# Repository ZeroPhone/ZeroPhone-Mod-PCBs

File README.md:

# ZeroPhone-Mod-PCBs
ZeroPhone mod board PCB files

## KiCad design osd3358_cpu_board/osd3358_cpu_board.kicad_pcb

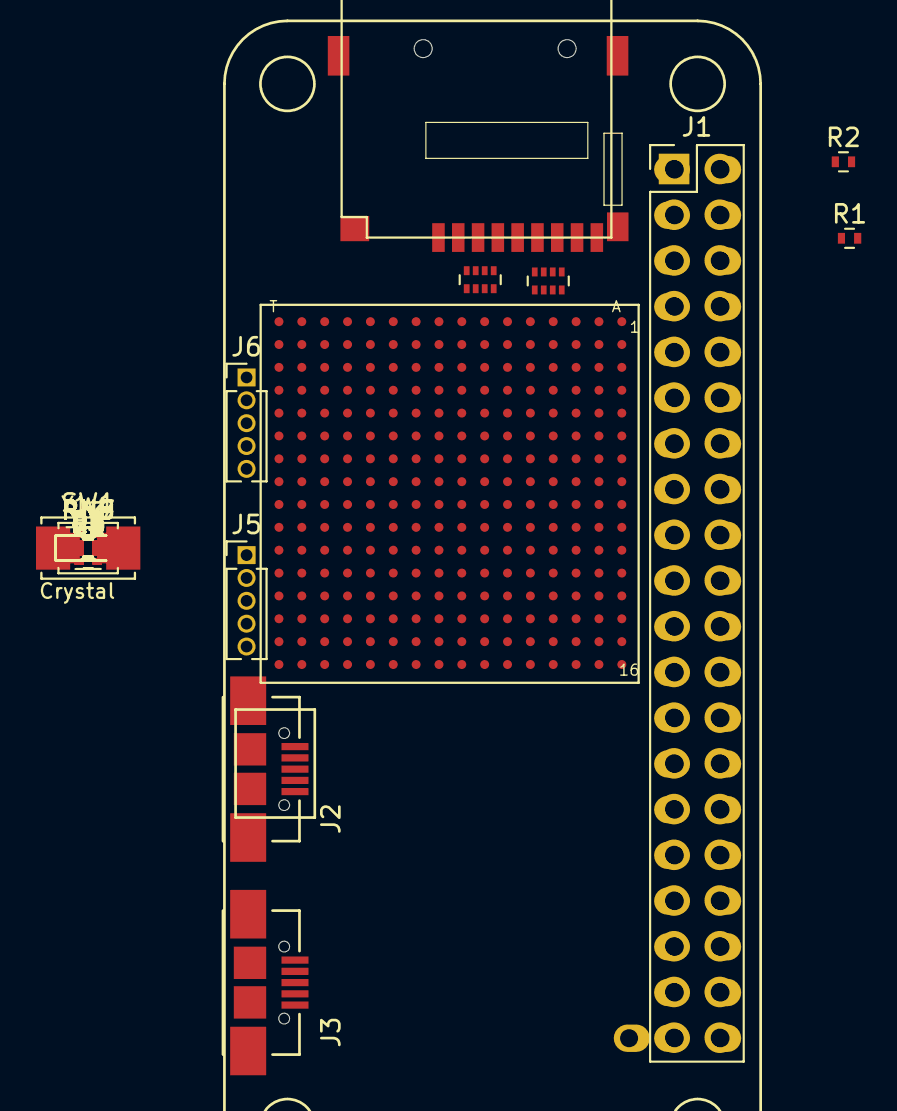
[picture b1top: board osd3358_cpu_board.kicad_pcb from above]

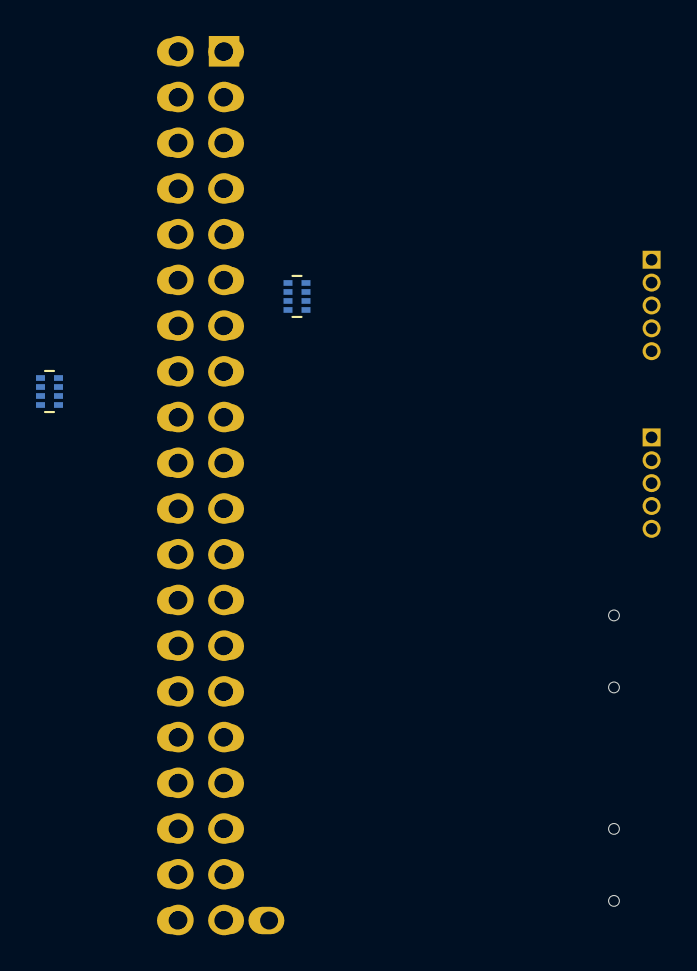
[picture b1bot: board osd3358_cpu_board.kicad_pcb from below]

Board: 2 copper layers, 37 parts (2 on the bottom side), 111 nets, no tracks yet.

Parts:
C1, C4: 100nF; C_0402
C2, C3: 18pF; C_0402
D1: PWR; LED_0805
D2: LED0; LED_0805
D3: LED1; LED_0805
D4: LED2; LED_0805
D5: LED3; LED_0805
J1: Conn_02x20_Odd_Even; Pin_Header_Straight_2x20_Pitch2.54mm
J2: USB_IN; MICROUSB_SIMPLE
J3: USB_OUT; MICROUSB_SIMPLE
J5: USB_PCTL; Pin_Header_Straight_1x05_Pitch1.27mm
J6: AIN_1.8V; Pin_Header_Straight_1x05_Pitch1.27mm
L1: 120R; C_0603
L2: Ferrite_Bead_Small; C_0603
R1, R2: 1.8K; R_0402
R3, R4, R5: 10K; R_0402
R6: 0R; R_0402
RN1, RN2, RN3, RN4, RN5, RN6, RN7, RN8: 10K; R_Array_Concave_4x0402
RN9: 1K; R_Array_Concave_4x0402
SW1: SW_Push; SW_SPST_B3U-1000P
U1: OSD3358-512M-BSM; OSD335X-BGA-256
U2: MICROSD
U3: 74AHC1G07; SOT-353_SC-70-5
U?: Pi0Top; Pi0-BACK
Y1: Crystal; CRYSTAL_5X3.2MM

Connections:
+1V8: U1.F10, U1.G10, U1.H10, U1.H11, U1.J10, U1.J11, U1.K10, U1.L10
+3.3VA: J1.1, J1.17, R1.1, R2.1, RN3.1, RN3.2, RN3.3, RN3.4, RN3.5, RN4.1, RN4.2, RN4.3, RN4.4, RN5.5, RN6.8, RN8.6, U1.F6, U1.F7, U1.G6, U1.G7, U2.4
+3.3VADC: D1.2, U1.F11, U1.G11
+3.3VP: U1.F8, U1.F9, U1.G8, U1.G9, U1.H7, U1.H8, U1.H9, U1.J7, U1.J8, U1.J9, U1.K8, U1.K9, U1.L8, U1.L9
+5V: J1.2, J1.4
+5VD: L1.2, U1.J16, U1.P9, U1.R9, U1.T9
+5VP: U1.K6, U1.K7, U1.L6, U1.L7
+BATT: U1.N7, U1.P8, U1.R8, U1.T8
+VDC: U1.P10, U1.R10, U1.T10
/EEP_WP: U1.M2, U1.N3
/LCD0: RN5.1, U1.G3
/LCD1: RN5.2, U1.G2
/LCD2: RN5.3, U1.G1
/LCD3: RN5.4, U1.H3
/LCD4: RN6.1, U1.H2
/LCD5: RN6.2, U1.H1
/LCD6: RN6.3, U1.J3
/LCD7: RN6.4, U1.J2
/LCD8: RN7.1, U1.J1
/LCD9: RN7.2, U1.K3
/LCD10: RN7.3, U1.K2
/LCD11: RN7.4, U1.K1
/LCD12: RN8.1, U1.L3
/LCD13: RN8.2, U1.L2
/LCD14: RN8.3, U1.L1
/LCD15: RN8.4, U1.M3
/PMIC_PGOOD: U1.N12, U1.P11, U3.2
/~RESET: U1.R11, U3.4
A0: RN1.7, RN1.8, U1.A8
A1: RN1.5, RN1.6, U1.B8
A2: RN2.7, RN2.8, U1.B6
A3: RN2.5, RN2.6, U1.C6
CS0: J1.24, U1.J14
CS1: J1.26, U1.A4
GND: C1.2, D2.1, D3.1, D4.1, D5.1, J1.6, J1.9, J1.14, J1.20, J1.25, J1.30, J1.34, J1.39, J2.5, J3.5, J5.3, J6.3, L2.2, R3.2, R4.1, R5.1, RN1.2, RN1.4, RN2.2, RN2.4, RN5.6, RN5.7, RN5.8, RN6.5, RN6.6, RN6.7, RN7.5, RN7.6, RN7.7, RN7.8, RN8.5, RN8.7, RN8.8, SW1.1, U1.D8, U1.D9, U1.E5, U1.E6, U1.E7, U1.E8, U1.E9, U1.E10, U1.E11, U1.E12, U1.F5, U1.F12, U1.G5, U1.G12, U1.H4, U1.H5, U1.H12, U1.H13, U1.J4, U1.J5, U1.J12, U1.J13, U1.K5, U1.K12, U1.L5, U1.L12, U1.M5, U1.M6, U1.M7, U1.M8, U1.M9, U1.M10, U1.M11, U1.M12, U1.N8, U1.N9, U2.6, U2.G1, U2.G2, U2.G3, U2.G4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
GP4: J1.7, RN2.3, U1.P5
GP5: J1.29, RN1.1, U1.T5
GP6: J1.31, RN1.3, U1.R5
GP12: J1.32, U1.T13
GP13: J1.33, U1.P12
GP16: J1.36, U1.P6
GP17: J1.11, RN2.1, U1.T4
I2S_BCK: J1.12, U1.A1
I2S_DIN: J1.38, U1.C4
I2S_DOUT: J1.40, U1.B1
I2S_LRCK: J1.35, U1.A2
ID_SC: J1.28, U1.B11
ID_SD: J1.27, R6.2, U1.A11
LED0: RN9.1, U1.P13
LED1: RN9.2, U1.T14
LED2: RN9.3, U1.R14
LED3: RN9.4, U1.P14
MISO: J1.21, U1.C12
MMC_CD: RN4.5, U1.C14, U2.9
MMC_CLK: RN4.8, U1.B15, U2.5
MMC_CMD: RN3.6, U1.B16, U2.3
MMC_D0: RN4.7, U1.A16, U2.7
MMC_D1: RN4.6, U1.A15, U2.8
MMC_D2: RN3.8, U1.C16, U2.1
MMC_D3: RN3.7, U1.C15, U2.2
MOSI: J1.19, U1.C13
unnamed: C2.1, U1.P16, Y1.1
unnamed: C2.2, C3.2, U1.N15
unnamed: C3.1, U1.N16, Y1.2
unnamed: D1.1, R4.2
unnamed: D2.2, RN9.8
unnamed: D3.2, RN9.7
unnamed: D4.2, RN9.6
unnamed: D5.2, RN9.5
unnamed: J2.1, L1.1
unnamed: J2.2, U1.K16
unnamed: J2.3, U1.K15
unnamed: J2.4, U1.K14
unnamed: J2.6, J3.6, L2.1
unnamed: J3.1, U1.M15
unnamed: J3.2, U1.L16
unnamed: J3.3, U1.L15
unnamed: J3.4, U1.L14
unnamed: J5.1, U1.L13
unnamed: J5.2, U1.M14
unnamed: J5.4, U1.J15
unnamed: J5.5, U1.K13
unnamed: J6.1, U1.C7
unnamed: J6.2, U1.C8
unnamed: J6.4, U1.C9
unnamed: J6.5, U1.N13
unnamed: R3.1, U1.M16
unnamed: SW1.2, U1.T11
unnamed: U1.N4, U1.N5
unnamed: U1.C10, U1.D10
unnamed: U1.C11, U1.D11
unnamed: U1.D4, U1.E4
unnamed: U1.D6, U1.D7
unnamed: U1.L4, U1.M4
unnamed: U1.N10, U1.N11
RXD: J1.10, U1.A12
SCK: J1.23, U1.C5
SCL: J1.5, R2.2, U1.A10
SDA: J1.3, R1.2, U1.B10
SDIO_CLK: J1.15, U1.D16
SDIO_CMD: J1.16, U1.G14
SDIO_D0: J1.18, U1.F16
SDIO_D1: J1.22, U1.G15
SDIO_D2: J1.37, U1.G16
SDIO_D3: J1.13, U1.F15
SD_EN: R6.1, U1.H16
TRST: R5.2, U1.D3
TXD: J1.8, U1.B12
VMEM: C1.1, U1.K11, U1.L11, U3.5
VREFN: C4.2, U1.A9, U1.B9
VREFP: C4.1, U1.A7, U1.B7

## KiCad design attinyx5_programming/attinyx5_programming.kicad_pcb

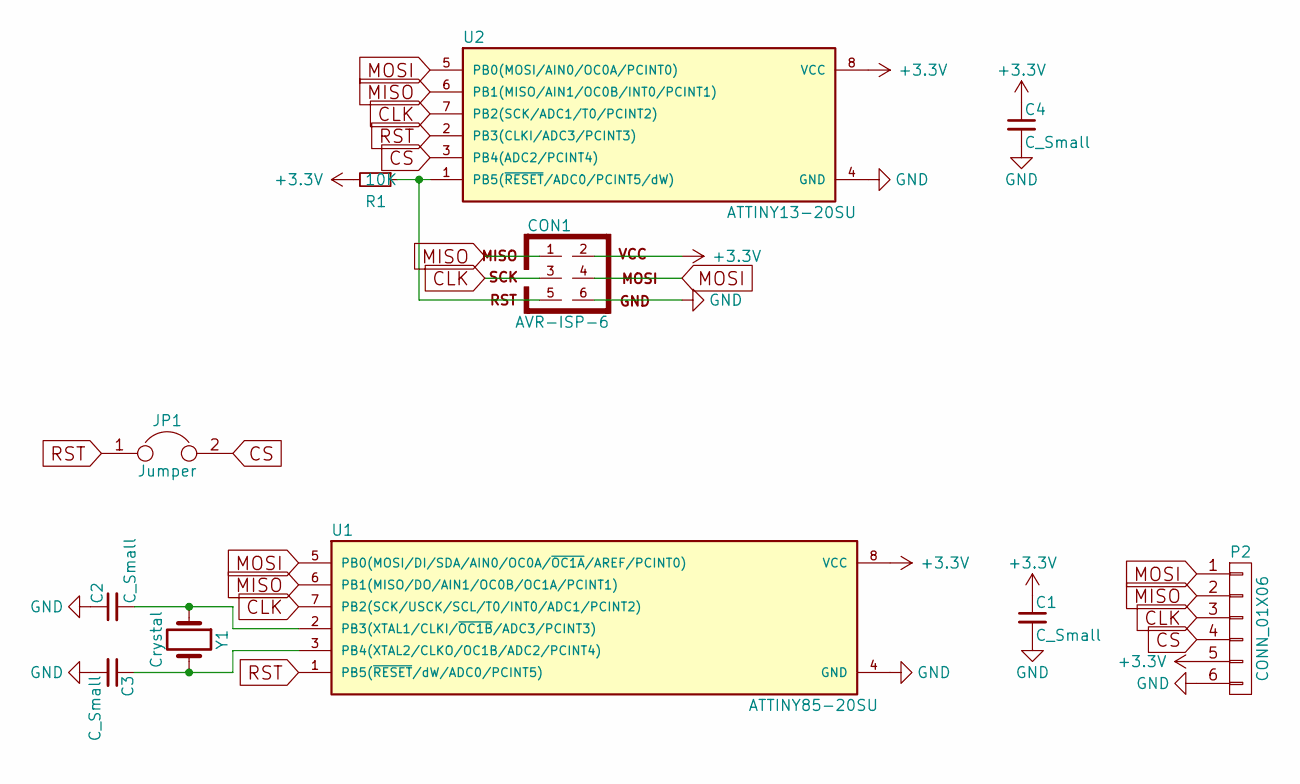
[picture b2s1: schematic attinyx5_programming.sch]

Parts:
C1, C2, C3, C4: C_Small; C_0805
CON1: AVR-ISP-6; Pin_Header_Straight_2x03_Pitch1.27mm_SMD
JP1: Jumper; GS2_SMALL
P2: CONN_01X06; Pin_Header_Straight_1x06_Pitch2.54mm
R1: 10K; R_0805
U1: ATTINY85-20SU; SSO-8_6.8x5.9mm_Pitch1.27mm_Clearance7mm
U2: ATTINY13-20SU; SSO-8_6.8x5.9mm_Pitch1.27mm_Clearance7mm
Y1: Crystal; Crystal_HC49-U_Vertical

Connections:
+3V3: C1.1, C4.1, CON1.2, P2.5, R1.2, U1.8 (VCC), U2.8 (VCC)
CLK: CON1.3, P2.3, U1.7 (PB2(SCK/USCK/SCL/T0/INT0/ADC1/PCINT2)), U2.7 (PB2(SCK/ADC1/T0/PCINT2))
CS: JP1.2, P2.4, U2.3 (PB4(ADC2/PCINT4))
GND: C1.2, C2.1, C3.2, C4.2, CON1.6, P2.6, U1.4 (GND), U2.4 (GND)
MISO: CON1.1, P2.2, U1.6 (PB1(MISO/DO/AIN1/OC0B/OC1A/PCINT1)), U2.6 (PB1(MISO/AIN1/OC0B/INT0/PCINT1))
MOSI: CON1.4, P2.1, U1.5 (PB0(MOSI/DI/SDA/AIN0/OC0A/~OC1A~/AREF/P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), U2.5 (PB0(MOSI/AIN0/OC0A/PCINT0))
unnamed: C2.2, U1.2 (PB3(XTAL1/CLKI/~OC1B~/ADC3/PCINT3)), Y1.1
unnamed: C3.1, U1.3 (PB4(XTAL2/CLKO/OC1B/ADC2/PCINT4)), Y1.2
unnamed: CON1.5, R1.1, U2.1 (PB5(~RESET~/ADC0/PCINT5/dW))
RST: JP1.1, U1.1 (PB5(~RESET~/dW/ADC0/PCINT5)), U2.2 (PB3(CLKI/ADC3/PCINT3))

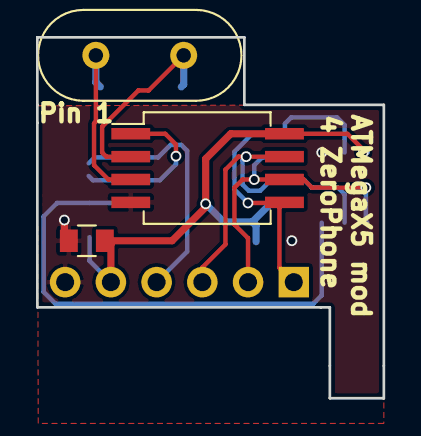
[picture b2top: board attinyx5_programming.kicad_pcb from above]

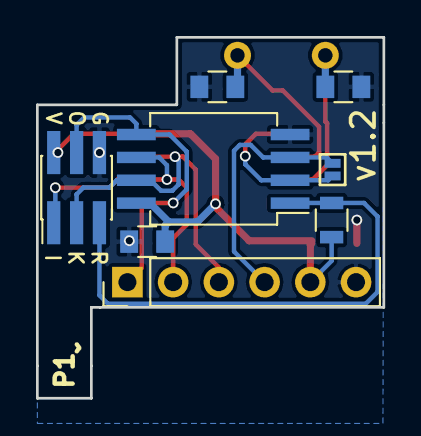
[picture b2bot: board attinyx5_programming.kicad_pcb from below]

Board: 2 copper layers, 19.2 x 20.0 mm, 11 parts (8 on the bottom side), 10 nets.

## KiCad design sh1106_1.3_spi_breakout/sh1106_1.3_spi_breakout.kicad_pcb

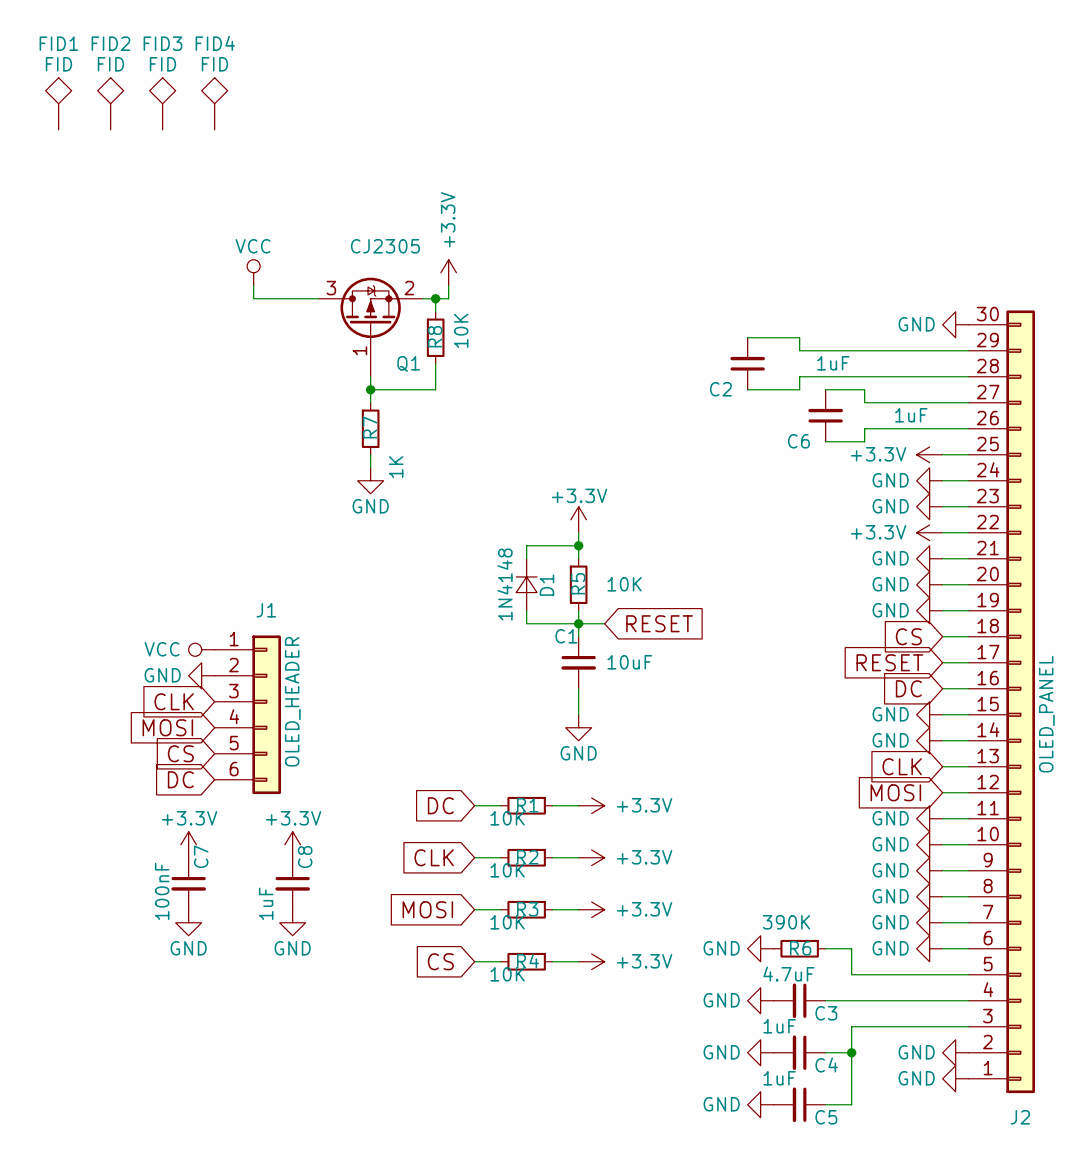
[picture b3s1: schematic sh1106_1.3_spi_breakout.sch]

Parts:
C1: 10uF; C_0805
C2, C4, C5, C6, C8: 1uF; C_0805
C3: 4.7uF; C_0805
C7: 100nF; C_0805
D1: 1N4148; D_0805
FID1, FID2, FID3, FID4: FID; Fiducial_0.75mm_Dia_1.5mm_Outer
J1: OLED_HEADER; Pin_Header_Straight_1x06_Pitch2.54mm
J2: OLED_PANEL; FPC_30_correct
Q1: CJ2305; SOT-23
R1, R2, R3, R4, R5, R8: 10K; R_0805
R6: 390K; R_0805
R7: 1K; R_0805

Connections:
+3V3: C7.1, C8.1, D1.1 (K), J2.22, J2.25, Q1.2 (S), R1.1, R2.1, R3.1, R4.1, R5.1, R8.1
CLK: J1.3, J2.13, R2.2
CS: J1.5, J2.18, R4.2
DC: J1.6, J2.16, R1.2
GND: C1.2, C3.2, C4.2, C5.2, C7.2, C8.2, J1.2, J2.1, J2.2, J2.6, J2.7, J2.8, J2.9, J2.10, J2.11, J2.14, J2.15, J2.19, J2.20, J2.21, J2.23, J2.24, J2.30, R6.2, R7.2
MOSI: J1.4, J2.12, R3.2
unnamed: C2.1, J2.28
unnamed: C2.2, J2.29
unnamed: C3.1, J2.4
unnamed: C4.1, C5.1, J2.3
unnamed: C6.1, J2.26
unnamed: C6.2, J2.27
unnamed: J2.5, R6.1
unnamed: Q1.1 (G), R7.1, R8.2
RESET: C1.1, D1.2 (A), J2.17, R5.2
VCC: J1.1, Q1.3 (D)

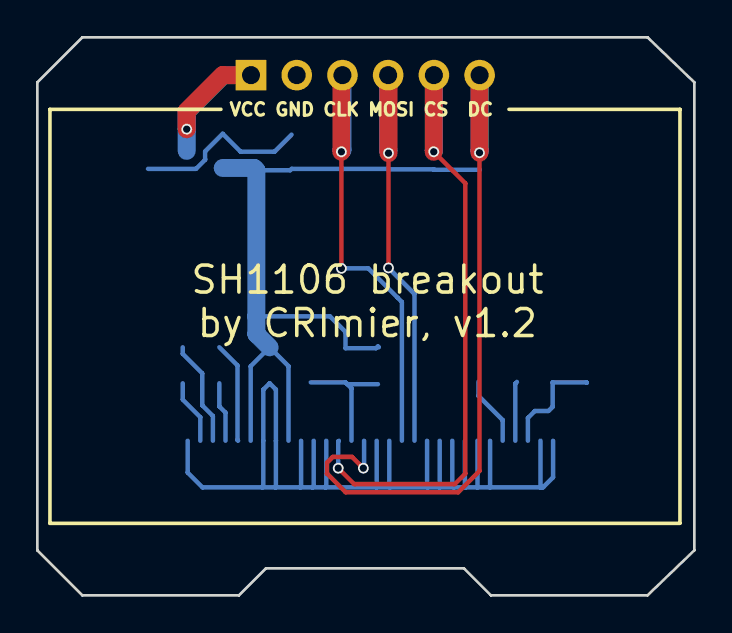
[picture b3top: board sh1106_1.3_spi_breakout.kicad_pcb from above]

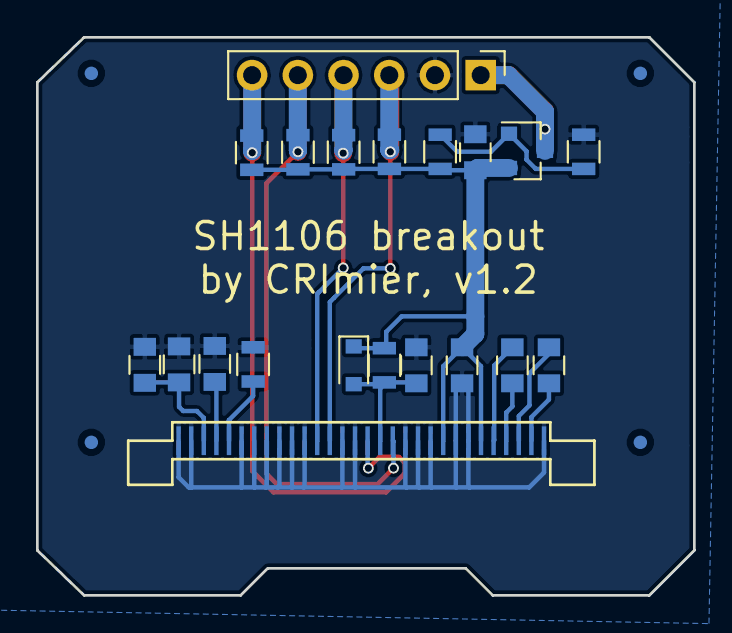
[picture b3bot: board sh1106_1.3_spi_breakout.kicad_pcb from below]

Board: 2 copper layers, 36.5 x 31.0 mm, 24 parts (24 on the bottom side), 16 nets.

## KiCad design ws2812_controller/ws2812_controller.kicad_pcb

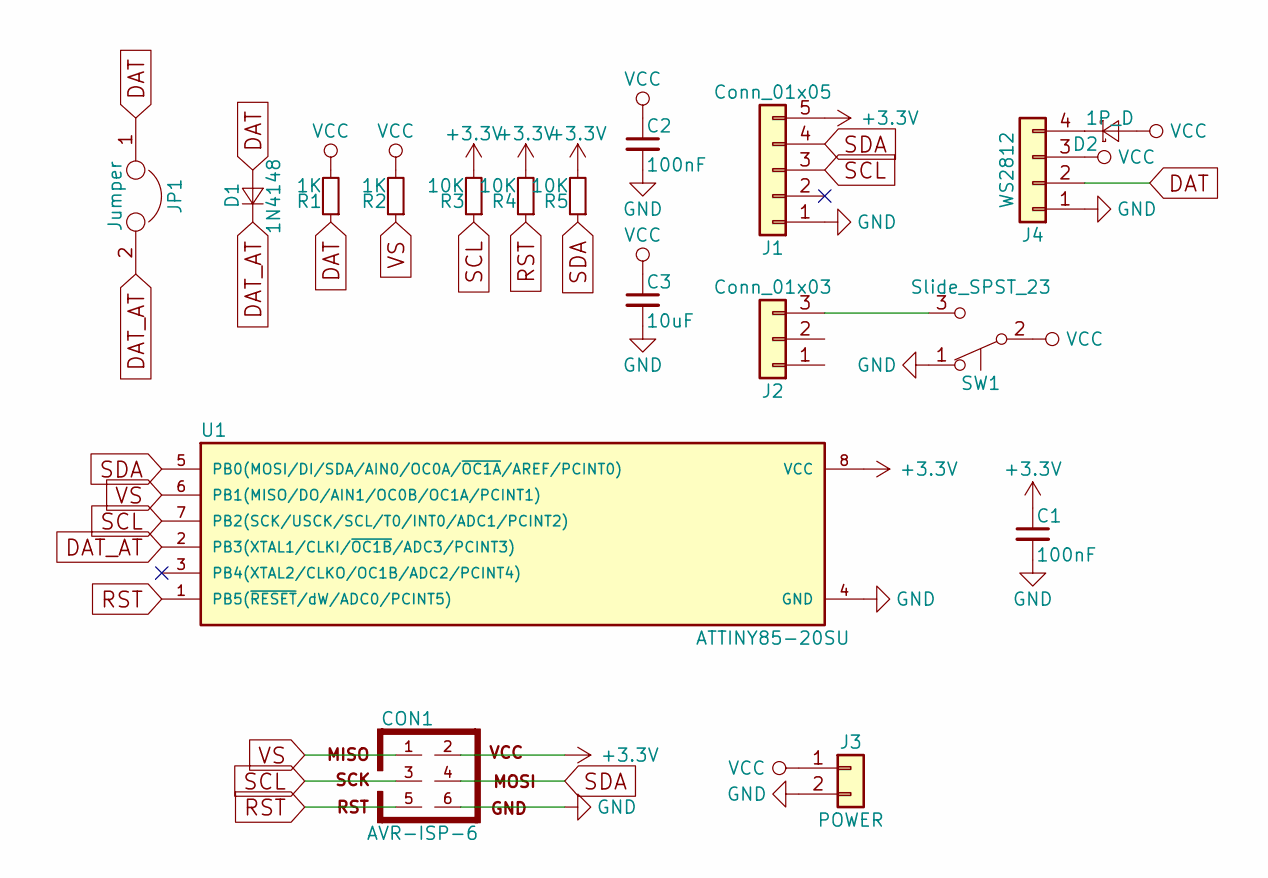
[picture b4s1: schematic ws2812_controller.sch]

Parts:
C1, C2: 100nF; C_0805
C3: 10uF; C_0805
CON1: AVR-ISP-6; Pin_Header_Straight_2x03_Pitch1.27mm_SMD
D1: 1N4148; D_MiniMELF
D2: 1P_D; D_MiniMELF
J1: Conn_01x05; Pin_Header_Straight_1x05_Pitch2.54mm
J2: Conn_01x03; Pin_Header_Straight_1x03_Pitch2.54mm
J3: POWER; Pin_Header_Straight_1x02_Pitch2.54mm
J4: WS2812; Pin_Header_Straight_1x04_Pitch2.54mm
JP1: Jumper; GS2_SMALL
R1, R2: 1K; R_0805
R3, R4, R5: 10K; R_0805
SW1: Slide_SPST_23; SW_SPDT_PCM12
U1: ATTINY85-20SU; SSO-8_6.8x5.9mm_Pitch1.27mm_Clearance7mm

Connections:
+3V3: C1.1, CON1.2, J1.5, R3.2, R4.2, R5.2, U1.8 (VCC)
DAT: D1.2 (A), J4.2, JP1.1, R1.1
DAT_AT: D1.1 (K), JP1.2, U1.2 (PB3(XTAL1/CLKI/~OC1B~/ADC3/PCINT3))
GND: C1.2, C2.2, C3.2, CON1.6, J1.1, J3.2, J4.1, SW1.1 (A), U1.4 (GND)
unnamed: D2.1 (K), J4.4
unnamed: J2.3, SW1.3 (C)
RST: CON1.5, R4.1, U1.1 (PB5(~RESET~/dW/ADC0/PCINT5))
SCL: CON1.3, J1.3, R3.1, U1.7 (PB2(SCK/USCK/SCL/T0/INT0/ADC1/PCINT2))
SDA: CON1.4, J1.4, R5.1, U1.5 (PB0(MOSI/DI/SDA/AIN0/OC0A/~OC1A~/AREF/P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)
VCC: C2.1, C3.1, D2.2 (A), J3.1, J4.3, R1.2, R2.2, SW1.2 (B)
VS: CON1.1, R2.1, U1.6 (PB1(MISO/DO/AIN1/OC0B/OC1A/PCINT1))

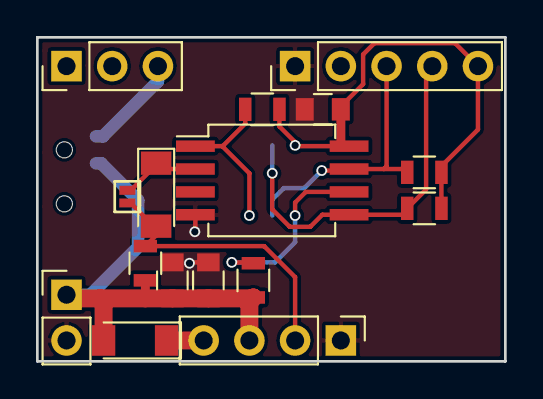
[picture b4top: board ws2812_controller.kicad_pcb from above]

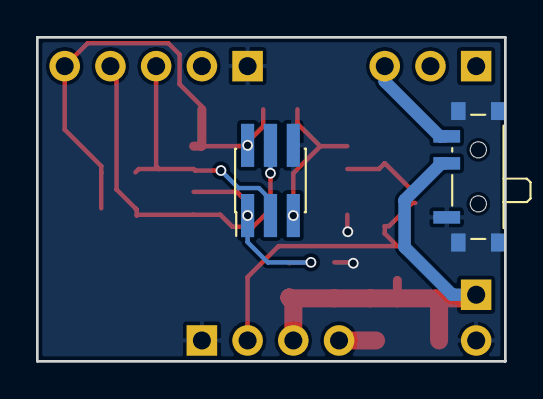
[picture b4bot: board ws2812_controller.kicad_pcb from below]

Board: 2 copper layers, 26.0 x 18.0 mm, 18 parts (2 on the bottom side), 11 nets.

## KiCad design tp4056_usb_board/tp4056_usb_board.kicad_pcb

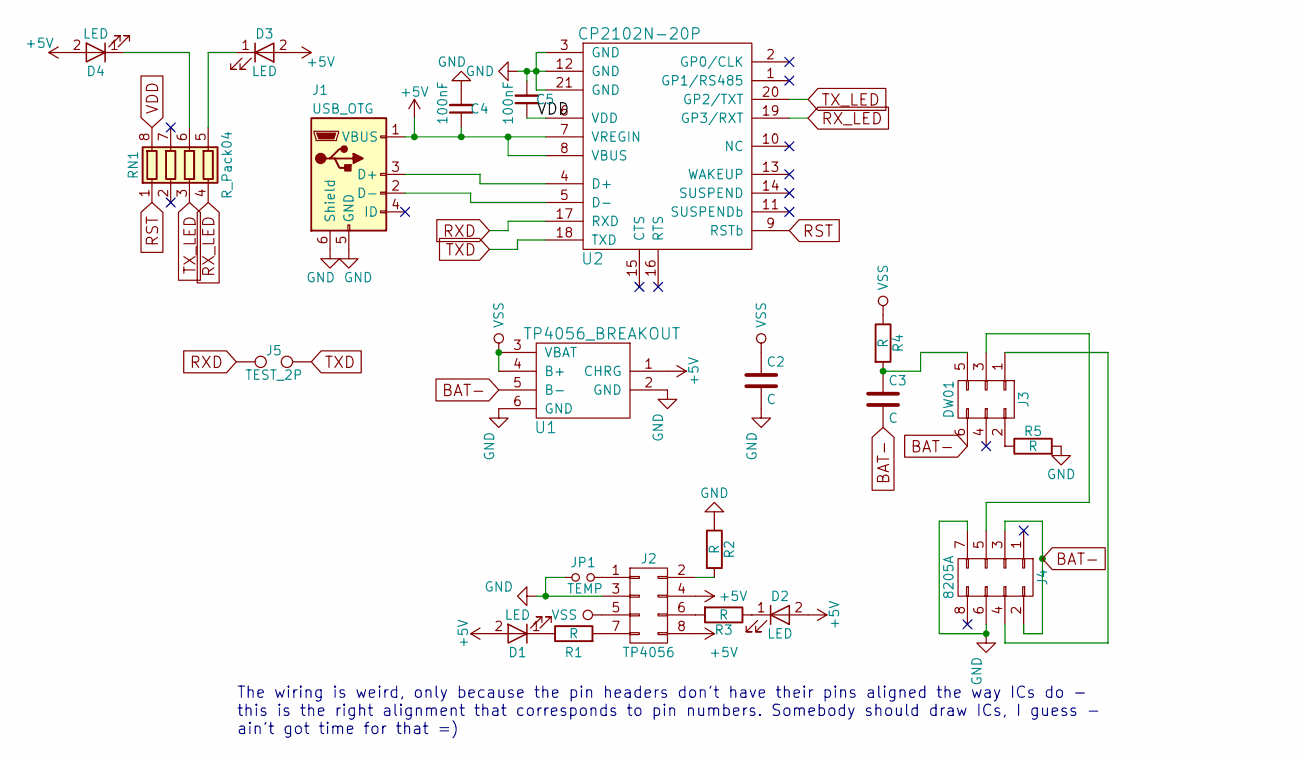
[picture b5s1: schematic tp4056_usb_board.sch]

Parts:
C2: C; C_0603
C3: C; C_0805
C4, C5: 100nF; C_0603
D1, D2, D3, D4: LED; LED_0805
J1: USB_OTG; MICROUSB_SIMPLE
J2: TP4056; SOIC-8_3.9x4.9mm_Pitch1.27mm
J3: DW01; SOT-23-6
J4: 8205A; TSSOP-8_4.4x3mm_Pitch0.65mm
J5: TEST_2P; Pin_Header_Straight_1x02_Pitch2.00mm
JP1: TEMP; GS2_SMALL
R1, R3, R4, R5: R; R_0603
R2: R; R_1206
RN1: R_Pack04; R_Array_Concave_4x0402
U1: TP4056_BREAKOUT
U2: CP2102N-20P; QFN-20-1EP_3x3mm_Pitch0.5

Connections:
+5V: C4.1, D1.2 (A), D2.2 (A), D3.2 (A), D4.2 (A), J1.1 (VBUS), J2.4, J2.8, U1.1 (CHRG), U2.7 (VREGIN), U2.8 (VBUS)
BAT-: C3.2, J3.6, J4.2, J4.3, U1.5 (B-)
GND: C2.2, C4.2, C5.2, J1.5 (GND), J1.6 (Shield), J2.3, J4.6, J4.7, JP1.1, R2.1, R5.2, U1.2 (GND), U1.6 (GND), U2.3 (GND), U2.12 (GND), U2.21 (GND)
unnamed: C3.1, J3.5, R4.2
unnamed: D1.1 (K), R1.1
unnamed: D2.1 (K), R3.1
unnamed: D3.1 (K), RN1.5 (R4.2)
unnamed: D4.1 (K), RN1.6 (R3.2)
unnamed: J1.2 (D-), U2.5 (D-)
unnamed: J1.3 (D+), U2.4 (D+)
unnamed: J2.1, JP1.2
unnamed: J2.2, R2.2
unnamed: J2.6, R3.2
unnamed: J2.7, R1.2
unnamed: J3.1, J4.4
unnamed: J3.2, R5.1
unnamed: J3.3, J4.5
RST: RN1.1 (R1.1), U2.9 (RSTb)
RXD: J5.1, U2.17 (RXD)
RX_LED: RN1.4 (R4.1), U2.19 (GP3/RXT)
TXD: J5.2, U2.18 (TXD)
TX_LED: RN1.3 (R3.1), U2.20 (GP2/TXT)
VDD: C5.1, RN1.8 (R1.2), U2.6 (VDD)
VSS: C2.1, J2.5, R4.1, U1.3 (VBAT), U1.4 (B+)

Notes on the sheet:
The wiring is weird, only because the pin headers don't have their pins aligned the way ICs do - this is the right alignment that corresponds to pin numbers. Somebody should draw ICs, I guess - ain't got time for that =)

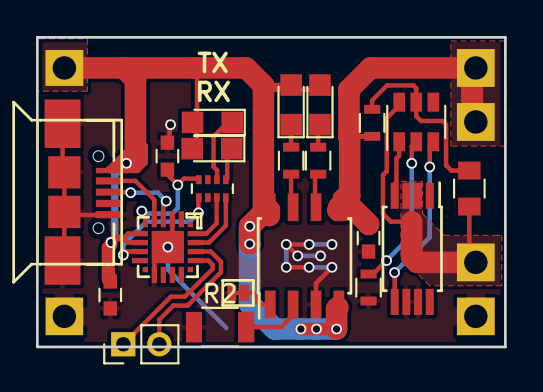
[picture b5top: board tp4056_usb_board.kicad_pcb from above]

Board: 2 copper layers, 26.0 x 17.2 mm, 22 parts (0 on the bottom side), 24 nets.

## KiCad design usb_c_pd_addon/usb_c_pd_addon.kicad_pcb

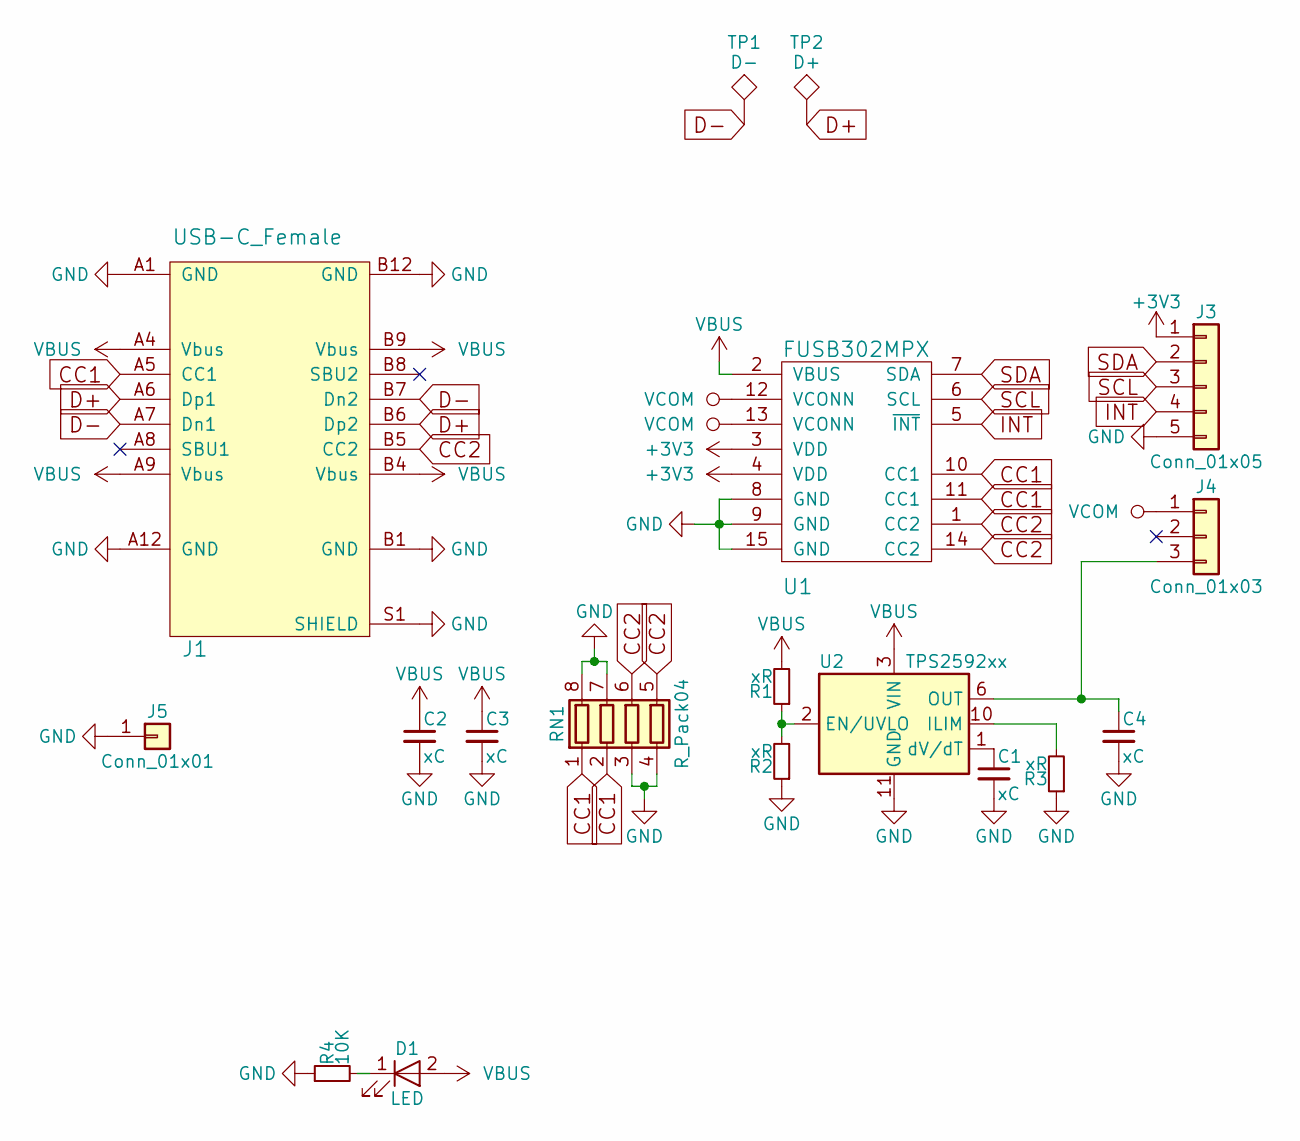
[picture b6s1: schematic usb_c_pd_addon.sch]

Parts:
C1: xC; C_0603_HandSoldering
C2, C3, C4: xC; C_0805_HandSoldering
D1: LED; LED_0805_HandSoldering
J1: USB-C_Female; USB_C_Receptacle_GT-USB-7010
J3: Conn_01x05; Pin_Header_Straight_1x05_Pitch2.54mm
J4: Conn_01x03; Pin_Header_Straight_1x03_Pitch2.54mm
J5: Conn_01x01; Pin_Header_Straight_1x01_Pitch2.54mm
R1, R2, R3: xR; R_0603_HandSoldering
R4: 10K; R_0603_HandSoldering
RN1: R_Pack04; R_Array_Convex_4x0603
TP1: D-; Measurement_Point_Round-SMD-Pad_Small
TP2: D+; Measurement_Point_Round-SMD-Pad_Small
U1: FUSB302MPX; MLP14
U2: TPS2592xx; VSON-10-1EP_3x3mm_P0.5mm_EP1.65x2.4mm_ThermalVias

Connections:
+3V3: J3.1, U1.3 (VDD), U1.4 (VDD)
CC1: J1.A5 (CC1), RN1.1 (R1.1), RN1.2 (R2.1), U1.10 (CC1), U1.11 (CC1)
CC2: J1.B5 (CC2), RN1.5 (R4.2), RN1.6 (R3.2), U1.1 (CC2), U1.14 (CC2)
D+: J1.A6 (Dp1), J1.B6 (Dp2), TP2.1
D-: J1.A7 (Dn1), J1.B7 (Dn2), TP1.1
GND: C1.2, C2.2, C3.2, C4.2, J1.A1 (GND), J1.A12 (GND), J1.B1 (GND), J1.B12 (GND), J1.S1 (SHIELD), J3.5, J5.1, R2.1, R3.1, R4.1, RN1.3 (R3.1), RN1.4 (R4.1), RN1.7 (R2.2), RN1.8 (R1.2), U1.8 (GND), U1.9 (GND), U1.15 (GND), U2.11 (GND)
INT: J3.4, U1.5 (~INT)
unnamed: C1.1, U2.1 (dV/dT)
unnamed: C4.1, J4.3, U2.6 (OUT), U2.7 (OUT), U2.8 (OUT)
unnamed: D1.1 (K), R4.2
unnamed: R1.1, R2.2, U2.2 (EN/UVLO)
unnamed: R3.2, U2.10 (ILIM)
SCL: J3.3, U1.6 (SCL)
SDA: J3.2, U1.7 (SDA)
VBUS: C2.1, C3.1, D1.2 (A), J1.A4 (Vbus), J1.A9 (Vbus), J1.B4 (Vbus), J1.B9 (Vbus), R1.2, U1.2 (VBUS), U2.3 (VIN), U2.4 (VIN), U2.5 (VIN)
VCOM: J4.1, U1.12 (VCONN), U1.13 (VCONN)

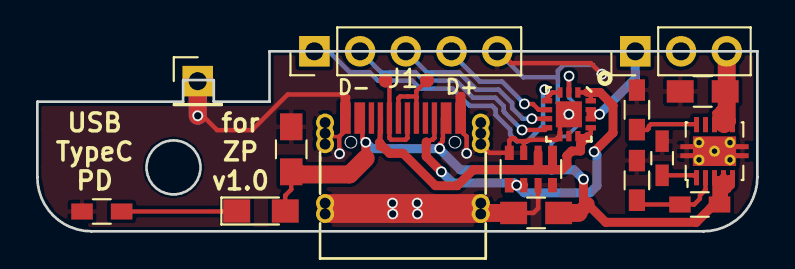
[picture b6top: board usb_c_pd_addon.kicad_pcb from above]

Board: 2 copper layers, 40.0 x 10.0 mm, 18 parts (0 on the bottom side), 16 nets.

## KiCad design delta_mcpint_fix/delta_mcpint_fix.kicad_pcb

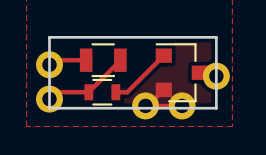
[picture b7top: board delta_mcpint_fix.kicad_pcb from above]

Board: 2 copper layers, 9.3 x 3.9 mm, 8 parts (0 on the bottom side), 5 nets.

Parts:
Q1: BC857; SOT-23
R1: 1K8; R_0603
R2: 10K; R_0805
TP1: VCC; Measurement_Point_Round-TH_Small
TP2: IN; Measurement_Point_Round-TH_Small
TP3: OUT; Measurement_Point_Round-TH_Small
TP4, TP5: GND; Measurement_Point_Round-TH_Small

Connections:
GND: Q1.2, TP4.1, TP5.1
unnamed: Q1.1, R1.1
unnamed: Q1.3, TP3.1
unnamed: R1.2, R2.2, TP2.1
VCC: R2.1, TP1.1

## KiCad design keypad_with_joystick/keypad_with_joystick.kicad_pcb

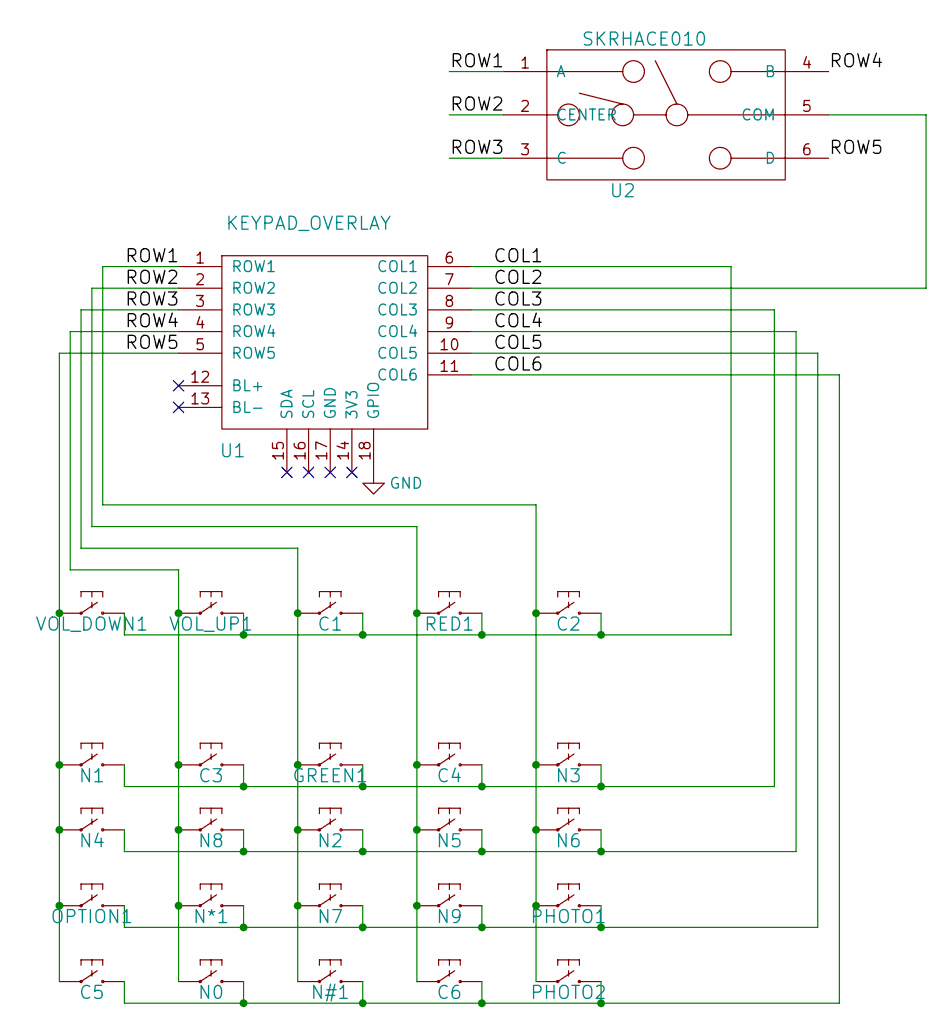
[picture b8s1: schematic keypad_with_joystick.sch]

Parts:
C1, C2, C3, C4, C5, C6: AB2_SWITCH_MOMENTARY; SW_SPST_EVQPE1
GREEN1: AB2_SWITCH_MOMENTARY; SW_SPST_EVQPE1
N0, N1, N2, N3, N4, N5, N6, N7, N8, N9: AB2_SWITCH_MOMENTARY; SW_SPST_SKQG
N#1: AB2_SWITCH_MOMENTARY; SW_SPST_SKQG
N*1: AB2_SWITCH_MOMENTARY; SW_SPST_SKQG
OPTION1: AB2_SWITCH_MOMENTARY; SW_SPST_EVQP7C
PHOTO1, PHOTO2: AB2_SWITCH_MOMENTARY; SW_SPST_EVQP7C
RED1: AB2_SWITCH_MOMENTARY; SW_SPST_EVQPE1
U1: KEYPAD_OVERLAY
U2: SKRHACE010
VOL_DOWN1: AB2_SWITCH_MOMENTARY; SW_SPST_EVQP7C
VOL_UP1: AB2_SWITCH_MOMENTARY; SW_SPST_EVQP7C

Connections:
/COL1: C1.2, C2.2, RED1.2, U1.6 (COL1), VOL_DOWN1.2, VOL_UP1.2
/COL2: U1.7 (COL2), U2.5 (COM)
/COL3: C3.2, C4.2, GREEN1.2, N1.2, N3.2, U1.8 (COL3)
/COL4: N2.2, N4.2, N5.2, N6.2, N8.2, U1.9 (COL4)
/COL5: N7.2, N9.2, N*1.2, OPTION1.2, PHOTO1.2, U1.10 (COL5)
/COL6: C5.2, C6.2, N0.2, N#1.2, PHOTO2.2, U1.11 (COL6)
/ROW1: C2.1, N3.1, N6.1, PHOTO1.1, PHOTO2.1, U1.1 (ROW1), U2.1 (A)
/ROW2: C4.1, C6.1, N5.1, N9.1, RED1.1, U1.2 (ROW2), U2.2 (CENTER)
/ROW3: C1.1, GREEN1.1, N2.1, N7.1, N#1.1, U1.3 (ROW3), U2.3 (C)
/ROW4: C3.1, N0.1, N8.1, N*1.1, U1.4 (ROW4), U2.4 (B), VOL_UP1.1
/ROW5: C5.1, N1.1, N4.1, OPTION1.1, U1.5 (ROW5), U2.6 (D), VOL_DOWN1.1
GND: U1.18 (GPIO)

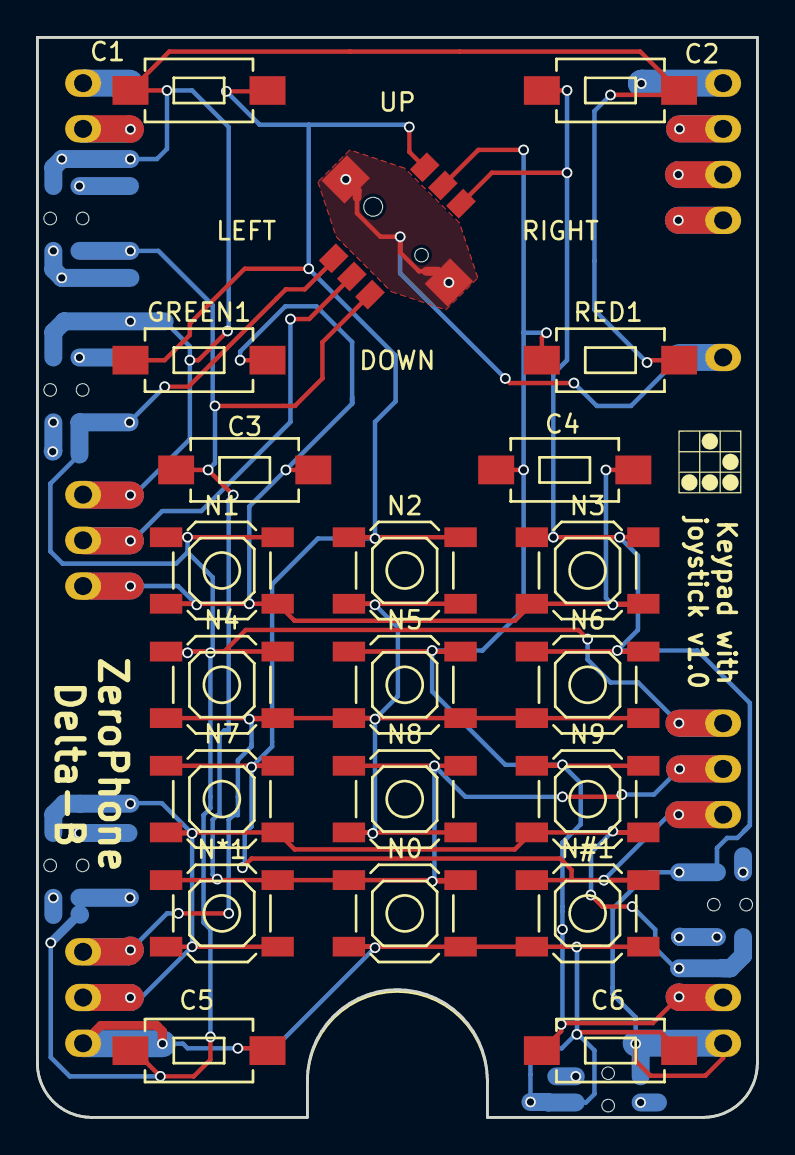
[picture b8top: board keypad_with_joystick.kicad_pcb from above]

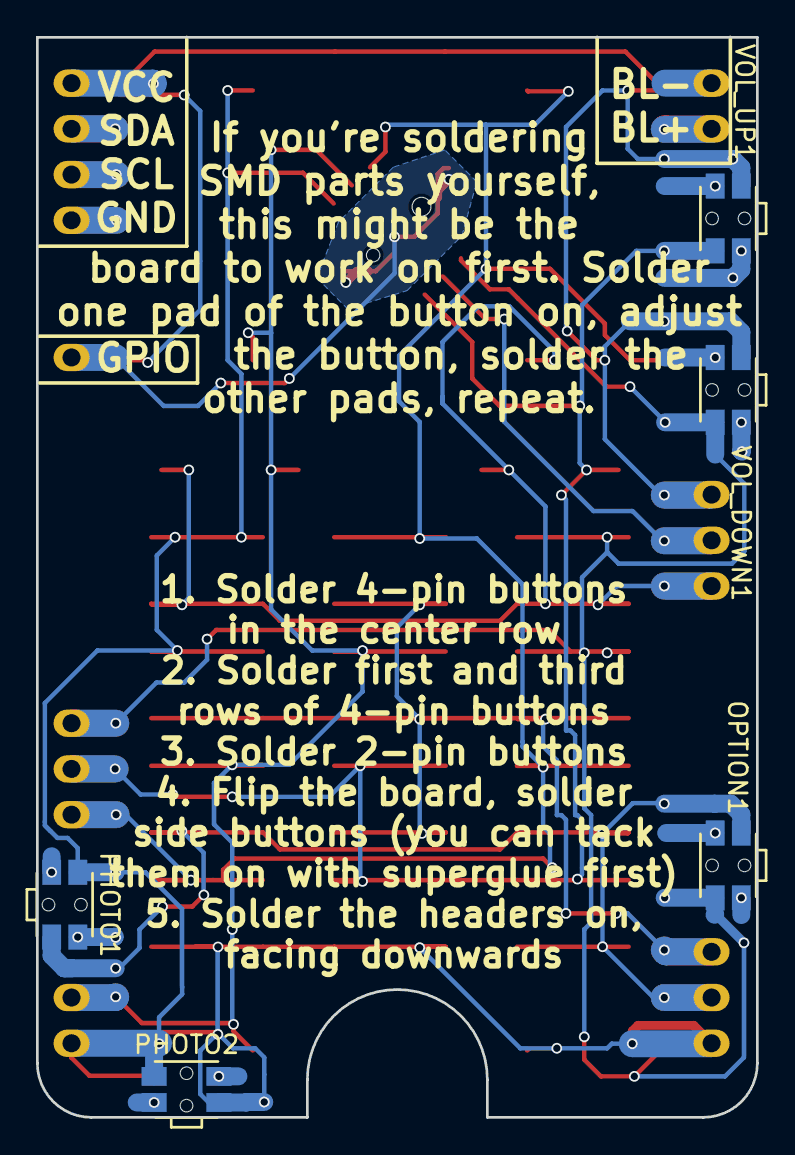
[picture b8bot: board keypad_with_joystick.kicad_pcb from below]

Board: 2 copper layers, 40.0 x 60.0 mm, 27 parts (5 on the bottom side), 11 nets.

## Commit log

2017-07-19 Updated gitignore
2017-07-19 Added ATMega ISP programming board
2017-07-19 Added audio buffer mod board
2017-07-19 Crypto EEPROM mod board - not finished yet
2017-07-19 ESP-12 board template added
2017-07-19 Added SPI flash SOIC8-W mod board
2017-07-19 Added ESP-12 LED+button mod board
2017-07-19 Added ESP12 ATMega mod board
2017-07-19 Sotto flex experiment files
2017-08-15 Simple IR receiver/transmitter mod board
2017-08-17 Added the 1.3" OLED breakout for SH1106 displays
2017-08-17 Started SPH0645 mod board
    To be finished once 13-pin header pinout is decided
2017-08-17 Small unsaved changes
2017-08-17 Accidentally committed file
2017-08-17 Added current sensor PCBs to mod boards
2017-08-17 Forgot a file
2017-08-18 Renaming a folder
2017-08-18 Moving SSD1332 breakout to mod board folder
2017-08-19 Added footprint for future mod board
2017-08-26 Renaming some files
2017-08-27 Adjusted dimensions, added silkscreen markings
2017-08-27 Starting work on TP4056+USB board - far from finished
2017-08-27 Started scrollwheel footprint
2017-08-27 Added RFM12/RFM01 breakout mod board
2017-08-27 Removed some dummy files that were accidentally added
2017-08-27 Forgot to commit some changes
2017-08-27 Fixed SPI flash mod board, added silkscreen helpers
2017-08-27 Mod board for 16-pin SPI flash programming
2017-08-27 Small update
2017-08-27 Started the charging+UART breakout
2017-08-28 ENC28J60 breakout adapter mod board
2017-08-28 24XX EEPROM programming mod board
2017-08-28 A new common footprint
2017-08-28 Updated crypto_eeprom board to not interfere with USB shield contacts on back board
2017-08-28 Changed the ATSHA breakout outline a bit more
2017-08-28 Changed gerber generation settings, added PCB text
2017-08-28 Not storing gerber files in repositories anymore
2017-08-28 Forgot to push license for flabbergast files, added
2017-08-28 Changed connector (to clean silkscreen)
    Also, fixed potential acid trap place
2017-08-29 Scrollwheel keypad mod - initial commit
2017-08-29 Added helper text and a missing track to 24xx mod
2017-08-29 Adding a CP2102N (20 pin version) symbol&footprint
2017-08-29 TP4056+UART board almost ready
    -Figure out UART castellation placement & add traces to there
    -Add thermal vias & mask openings
    -Check pads on corners - convert to rectangle pads & enlarge holes
    -Verify everything once again against the original boards
2017-08-31 Updated audio buffer board
    -Changed power regulator to a low-noise one
    -Moved GND testpoint so that adding a connector is theoretically
    possible, just in case
    -Added auxiliary axis
2017-08-31 Renamed files
2017-08-31 Removing gerbers from repo
2017-08-31 Changed default gerber output directory
2017-08-31 Finished TP4056 charging+USB-UART board
2017-09-01 Added text with LED color-to-signal info
2017-09-02 SIM5320 breakout - work almost done
    -SIM card slot missing
    -u.FL connectors missing
    -footprint not yet changed to SIM800 footprint
2017-09-05 Finished I2S microphone mod board
2017-09-05 Adding u.FL to SIM53x0 board - no antenna traces yet
2017-09-05 Removing gerbers
2017-09-05 Updated footprint for SPI connector
2017-10-10 Adding schematic plots
2018-02-16 Changed layout/UART header for the new back board
2018-03-09 New version of the SIM5X30 breakout - adjusted for Delta boards
    Needs to be printed out to see clearances
    No SIM slot footprint yet
    No SIM5320, u.FL and SIM slot 3D models
2018-03-09 add 3D model of u.FL connector to 3G modem board
2018-03-09 design SIM5320 model in OpenSCAD
2018-03-09 export SIM5320 model as STL
2018-03-09 fix SIM5320 model with meshconv
2018-03-09 convert SIM5320 .stl to .wrl
2018-03-09 add SIM5320 3D model to board
2018-03-12 Adding symbol&footprint for the common MicroSIM holder from China
2018-03-12 Adding back board outline footprint - for designing replacement modem boards
2018-03-12 Adding the SIM5300EA footprint
2018-03-12 Finished board - has limited usability! 3G modem too big
2018-03-12 Forgot headers for 3G modem - adding
2018-03-12 Renaming the TP4056 board files + small fixups
2018-03-15 Added version information
2018-03-15 Added version information, updated pinout
2018-03-15 Adding SIM5300 breakout - ready
2018-03-30 Redesigned to use new footprint and UDFN IC
2018-03-30 No longer sticks out of the ZP outline, no longer flush to back PCB
2018-03-30 Finished the keypad+scrollwheel board - needs to be printed out
2018-03-30 Fixed DRC violations and changed the pinout a little bit
2018-03-30 Fixed pin header 3D model offsets
2018-03-30 Added some stub traces to fix non-connects
2018-03-30 Fixing non-connects in ESP12 mod board template
2018-03-30 Git-ignoring all gerber files by extension
2018-03-30 Removing gerber files from repo
2018-03-30 Updating I2C pinout in 24xx EEPROM board
2018-03-30 Changing silkscreen text
2018-03-30 Minor adjustments
2018-03-30 Minor silkscreen adjustments
2018-04-03 Adding the 3.5" dispkay adapter board
2018-04-03 Adjusted silkscreen
2018-04-03 Added the NRF24L01 adapter
2018-04-03 Adding the TP4056 stub board (no actual TP4056)
2018-04-03 Small silkscreen adjustments
2018-04-03 3D model adjustments
2018-04-03 Small routing adjustments
2018-05-02 Adding the RC522 adapter
2018-05-02 Fixing the schematic - adding a jumper (instead of the capacitor) to the TEMP pin
2018-05-02 Adding the universal level shifter board
2018-05-02 Forgot to add the GTL2003 symbol, added
2018-05-02 DC-DC USB hub board - not completely finished (fucked up orientation)
2018-05-02 The "Dock" board for Gamma boards (not finished, need to check USB connector position)
2018-05-24 Adding the VEML6070 (UVB) sensor adapter
2018-05-24 Adding the QWIIC socket adapter
2018-05-24 Adding the GSM modem signal/power breakout board
2018-05-24 Level shifter finished and fixed - swapping the MCP for 1117
2018-05-24 Adding the GY series sensor adapter
2018-05-24 Updating the keypad+scrollwheel board to have correct footprint&stronger traces
2018-05-24 Adding the ESP12-footprint MicroSD slot
2018-05-24 Tying XTAL pins to ground
2018-05-24 Delta dock board finished
2018-05-24 Adding dock board for Gamma boards
2018-05-24 Adding the ATTiny programming board
2018-05-24 Adding the 93xXX programming board
2018-05-24 Finished the GL850G-based USB hub&DCDC board
2018-05-24 Adding the FE1.1s-based USB hub&DCDC board
2018-10-20 USB Type-C PD addon - v1.0
2018-10-20 Bottom "power board" outline footprint added
2019-01-30 Giving the 24xx SO8 board a new name, changing the passive footprints, adding +- on the silkscreen
2019-01-30 Added a breakout for the 24xx DFN EEPROMs
2019-01-30 Added a breakout for 24xx DFN EEPROMs
2019-01-30 Adding the common DFN8 EEPROM footprint
2019-01-30 Dock board v1.1 - fixing the dock board outline and positioning
2019-01-30 Adding the "gadget power adapter" mod
2019-01-30 Adding the "keypad with joystick" mod, v1.0
2019-01-30 Adding the Delta MCPINT fix PCB
2019-01-30 Working on the OSD3358 CPU board - pin assignment finished, board layout viability evaluated
2019-01-30 Gitignore-ing the pocketbeagle repo in OSD3358 board
2019-01-30 Git-ignoring .zip files
2019-01-30 USB Type-C mod - v1.0
2019-01-30 Gitignore-ing .svg files
2019-01-30 TP4056 board - changing current set resistor FP to 1206 (better change to 0805 in the next rev?)
2019-01-30 Adding the WS2812 controller mod
2019-01-30 Fixing the FPC connector on the SH1106 PCB - v1.2
2019-01-30 v1.1 of ATTiny PCB - fixing the ATTiny FP, adding an additional ATTIny to track the RST pin
2019-04-19 Today's work
